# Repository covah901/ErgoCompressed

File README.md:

# ErgoCompressed
Making Ergodone smaller without sacrificing functionality.

based on :ErgoDone

Original work by Dox. K.T.E.C. present.
# Lisence
GPL v3

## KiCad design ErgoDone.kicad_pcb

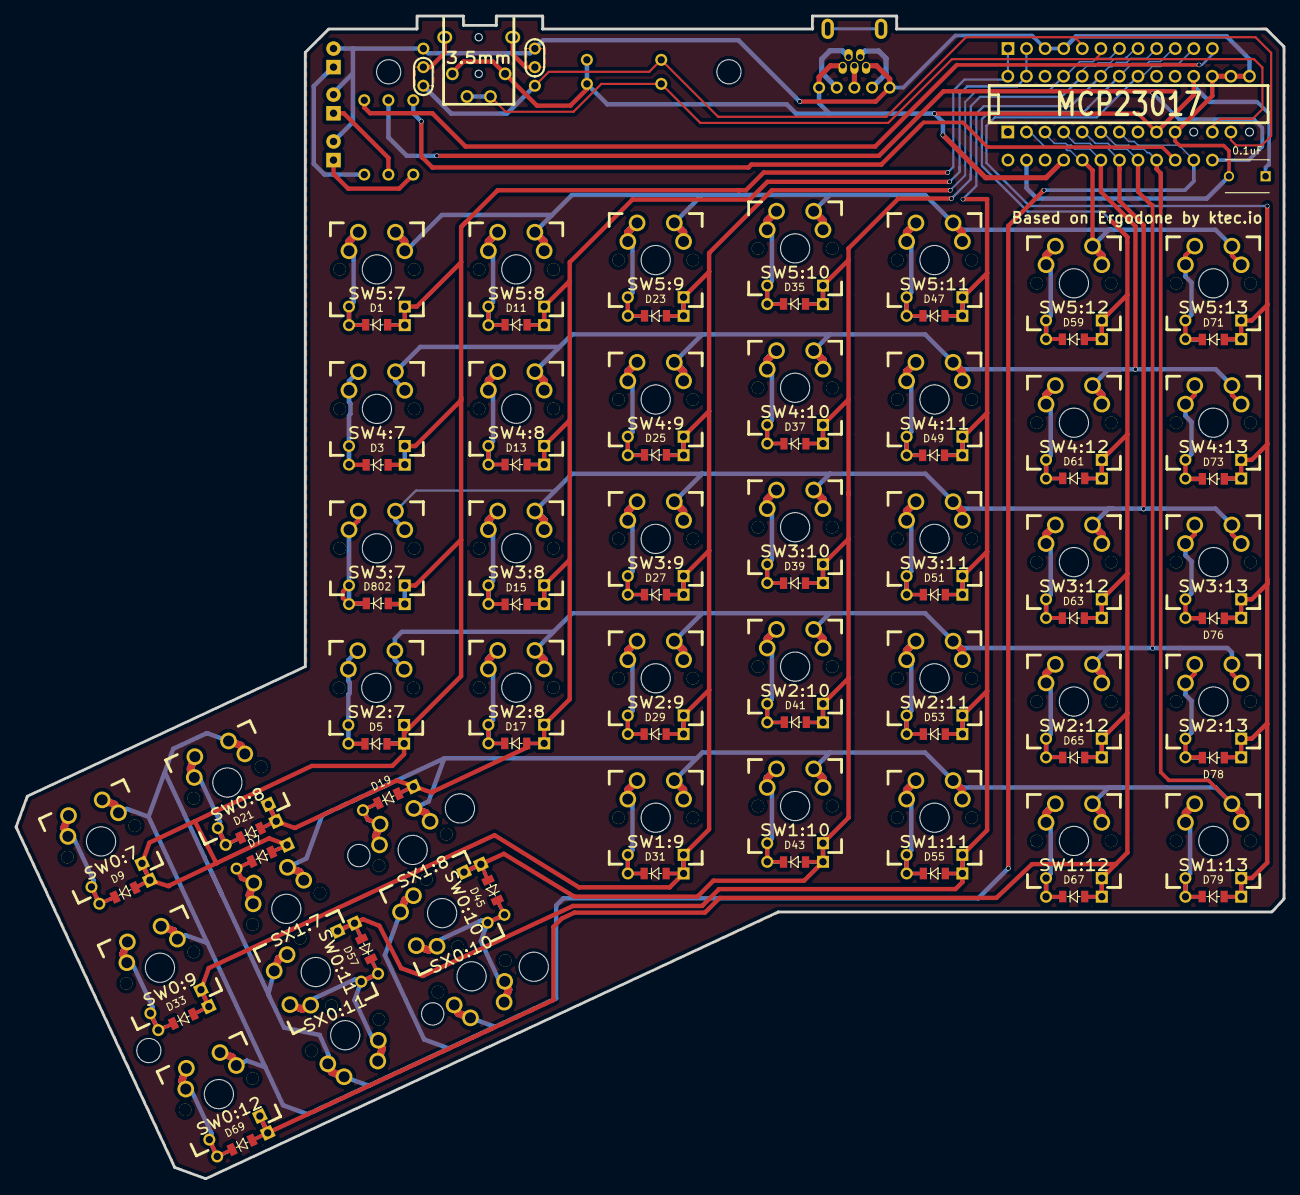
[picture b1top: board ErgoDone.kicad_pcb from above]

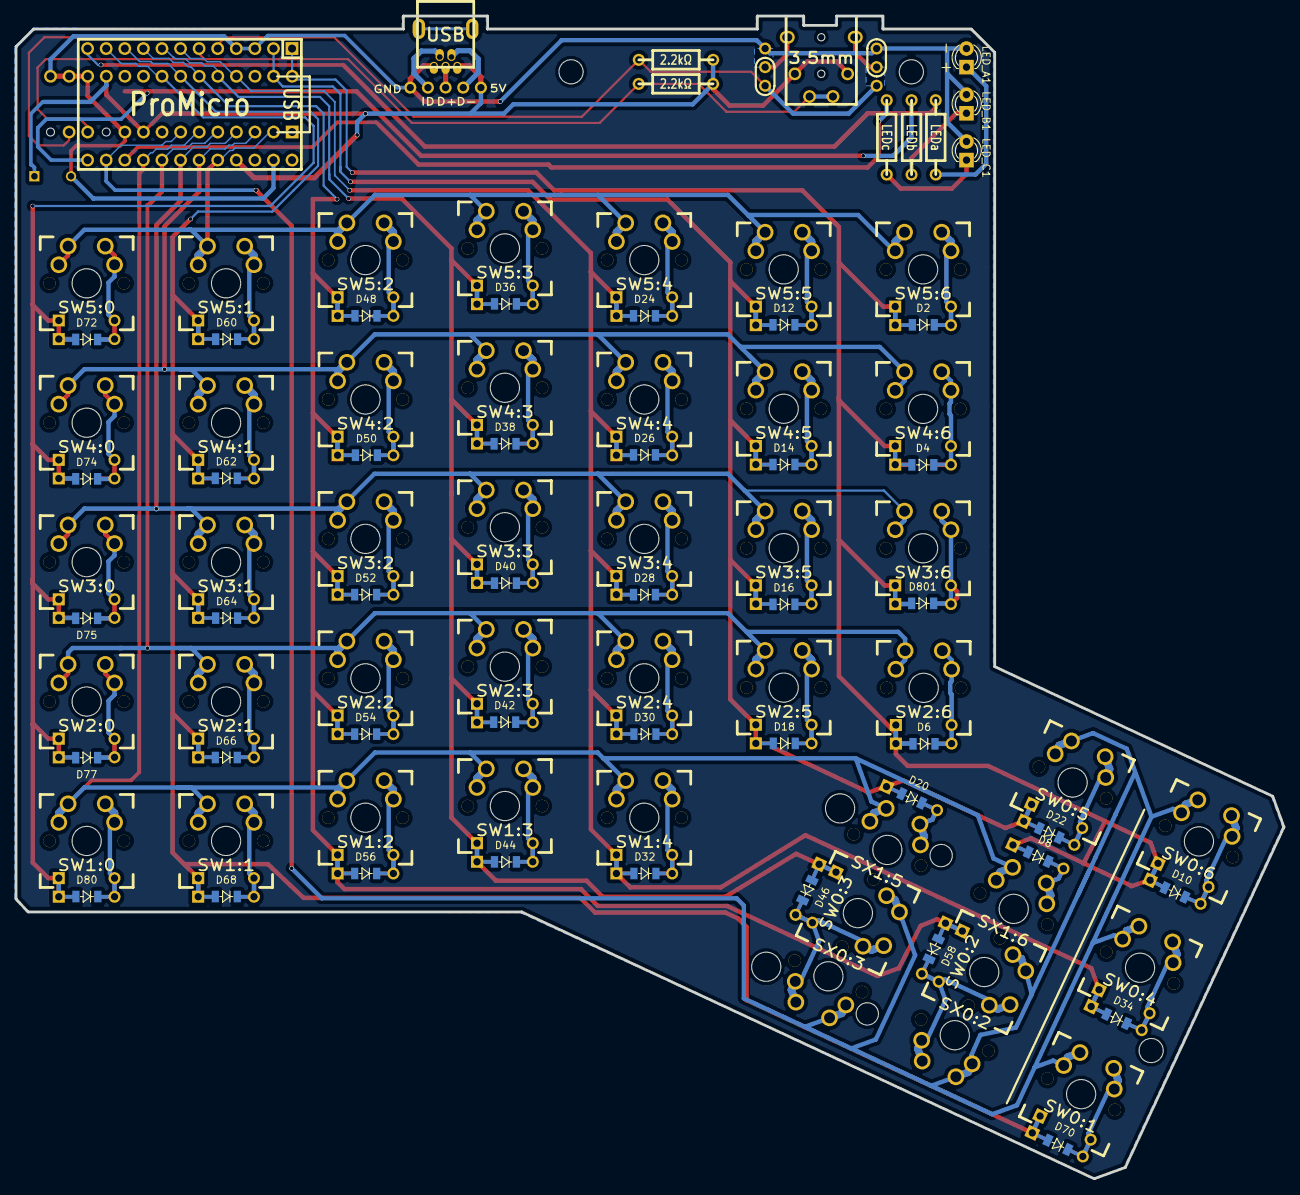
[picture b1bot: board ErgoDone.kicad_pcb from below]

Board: 2 copper layers, 173.3 x 158.9 mm, 143 parts (52 on the bottom side), 66 nets.

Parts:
C1: 0.1uF; C_Disc_D6_P5
D1, D3, D5, D7, D9, D11, D13, D15, D17, D19, D21, D23, D25, D27, D29, D31, D33, D35, D37, D39, D41, D43, D45, D47, D49, D51, D53, D55, D57, D59, D61, D63, D65, D67, D69, D71, D73, D75, D77, D79, D802: DIODE; D_1206_L
D2, D4, D6, D8, D10, D12, D14, D16, D18, D20, D22, D24, D26, D28, D30, D32, D34, D36, D38, D40, D42, D44, D46, D48, D50, D52, D54, D56, D58, D60, D62, D64, D66, D68, D70, D72, D74, D76, D78, D80, D801: DIODE; D_1206_R
D81, D82: DIODE; DIODE_SX
J1: USB; USBMINImod
J2: 3.5mm; 4pin35mmAudio
J3, J4: JMP; 100PITCH1X3
LED_A1: LEDa; ERGO_LED-3MM
LED_B1: LEDb; ERGO_LED-3MM
LED_C1: LEDc; ERGO_LED-3MM
R1, R2: 2.2kΩ; ERGO_RESISTOR
RA1: LEDa; ERGO_RESISTOR
RB1: LEDb; ERGO_RESISTOR
RC1: LEDc; ERGO_RESISTOR
S2: STAB200; STAB_PCB940
SW0:7: SW0:6; MX_FLIP_DIODE_NOSMD
SW0:8: SW0:5; MX_FLIP_DIODE_NOSMD
SW0:9: SW0:4; MX_FLIP_DIODE_NOSMD
SW0:10: SW0:3; MX_FLIP_DIODE_NOSMD
SW0:11: SW0:2; MX_FLIP_DIODE_NOSMD
SW0:12: SW0:1; MX_FLIP_DIODE_NOSMD
SW1:9: SW1:4; MX_FLIP_DIODE_NOSMD
SW1:10: SW1:3; MX_FLIP_DIODE_NOSMD
SW1:11: SW1:2; MX_FLIP_DIODE_NOSMD
SW1:12: SW1:1; MX_FLIP_DIODE_NOSMD
SW1:13: SW1:0; MX_FLIP_DIODE_NOSMD
SW2:7: SW2:6; MX_FLIP_DIODE_NOSMD
SW2:8: SW2:5; MX_FLIP_DIODE_NOSMD
SW2:9: SW2:4; MX_FLIP_DIODE_NOSMD
SW2:10: SW2:3; MX_FLIP_DIODE_NOSMD
SW2:11: SW2:2; MX_FLIP_DIODE_NOSMD
SW2:12: SW2:1; MX_FLIP_DIODE_NOSMD
SW2:13: SW2:0; MX_FLIP_DIODE_NOSMD
SW3:7: SW3:6; MX_FLIP_DIODE_NOSMD
SW3:8: SW3:5; MX_FLIP_DIODE_NOSMD
SW3:9: SW3:4; MX_FLIP_DIODE_NOSMD
SW3:10: SW3:3; MX_FLIP_DIODE_NOSMD
SW3:11: SW3:2; MX_FLIP_DIODE_NOSMD
SW3:12: SW3:1; MX_FLIP_DIODE_NOSMD
SW3:13: SW3:0; MX_FLIP_DIODE_NOSMD
SW4:7: SW4:6; MX_FLIP_DIODE_NOSMD
SW4:8: SW4:5; MX_FLIP_DIODE_NOSMD
SW4:9: SW4:4; MX_FLIP_DIODE_NOSMD
SW4:10: SW4:3; MX_FLIP_DIODE_NOSMD
SW4:11: SW4:2; MX_FLIP_DIODE_NOSMD
SW4:12: SW4:1; MX_FLIP_DIODE_NOSMD
SW4:13: SW4:0; MX_FLIP_DIODE_NOSMD
SW5:7: SW5:6; MX_FLIP_DIODE_NOSMD
SW5:8: SW5:5; MX_FLIP_DIODE_NOSMD
SW5:9: SW5:4; MX_FLIP_DIODE_NOSMD
SW5:10: SW5:3; MX_FLIP_DIODE_NOSMD
SW5:11: SW5:2; MX_FLIP_DIODE_NOSMD
SW5:12: SW5:1; MX_FLIP_DIODE_NOSMD
SW5:13: SW5:0; MX_FLIP_DIODE_NOSMD
SX0:10: SX0:3; MX_FLIP
SX0:11: SX0:2; MX_FLIP
SX1:7: SX1:6; MX_FLIP
SX1:8: SX1:5; MX_FLIP
U1: ProMicro
U2: MCP23017

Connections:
/COL0: D71.2, D72.2, D73.2, D74.2, D75.2, D76.2, D77.2, D78.2, D79.2, D80.2, SW1:13.4, SW2:13.4, SW3:13.4, SW4:13.4, SW5:13.4, U1.11, U2.21
/COL1: D59.2, D60.2, D61.2, D62.2, D63.2, D64.2, D65.2, D66.2, D67.2, D68.2, D69.2, D70.2, SW0:12.4, SW1:12.4, SW2:12.4, SW3:12.4, SW4:12.4, SW5:12.4, U1.10, U2.22
/COL4: D23.2, D24.2, D25.2, D26.2, D27.2, D28.2, D29.2, D30.2, D31.2, D32.2, D33.2, D34.2, SW0:9.4, SW1:9.4, SW2:9.4, SW3:9.4, SW4:9.4, SW5:9.4, U1.7, U2.25
/COL5: D11.2, D12.2, D13.2, D14.2, D15.2, D16.2, D17.2, D18.2, D19.2, D20.2, D21.2, D22.2, D82.2, SW0:8.4, SW2:8.4, SW3:8.4, SW4:8.4, SW5:8.4, U1.2, U2.27
/COL6: D1.2, D2.2, D3.2, D4.2, D5.2, D6.2, D7.2, D8.2, D9.2, D10.2, D81.2, D801.2, D802.2, SW0:7.4, SW2:7.4, SW3:7.4, SW4:7.4, SW5:7.4, U1.1, U2.28
/COL10: D35.2, D36.2, D37.2, D38.2, D39.2, D40.2, D41.2, D42.2, D43.2, D44.2, D45.2, D46.2, SW0:10.4, SW1:10.4, SW2:10.4, SW3:10.4, SW4:10.4, SW5:10.4, U1.8, U2.24
/COL11: D47.2, D48.2, D49.2, D50.2, D51.2, D52.2, D53.2, D54.2, D55.2, D56.2, D57.2, D58.2, SW0:11.4, SW1:11.4, SW2:11.4, SW3:11.4, SW4:11.4, SW5:11.4, U1.9, U2.23
/LED_A: RA1.1, U1.12
/LED_B: RB1.1, U1.18
/LED_C: RC1.1, U1.20
/ROW0: SW0:7.1, SW0:8.1, SW0:9.1, SW0:10.1, SW0:11.1, SW0:12.1, SX0:10.1, SX0:11.1, U1.19, U2.7
/ROW1: SW1:9.1, SW1:10.1, SW1:11.1, SW1:12.1, SW1:13.1, SX1:7.1, SX1:8.1, U1.21, U2.6
/ROW2: SW2:7.1, SW2:8.1, SW2:9.1, SW2:10.1, SW2:11.1, SW2:12.1, SW2:13.1, U1.22, U2.5
/ROW3: SW3:7.1, SW3:8.1, SW3:9.1, SW3:10.1, SW3:11.1, SW3:12.1, SW3:13.1, U1.23, U2.4
/ROW4: SW4:7.1, SW4:8.1, SW4:9.1, SW4:10.1, SW4:11.1, SW4:12.1, SW4:13.1, U1.24, U2.3
/ROW5: SW5:7.1, SW5:8.1, SW5:9.1, SW5:10.1, SW5:11.1, SW5:12.1, SW5:13.1, U1.25, U2.2
/SCLM: J2.3, J2.5, R2.2, U1.6, U2.12
/SDAM: J3.1, J4.1, R1.2, U1.5, U2.13
GND: C1.2, J1.5, J3.3, J4.3, LED_A1.2, LED_B1.2, LED_C1.2, U1.3, U1.4, U1.28, U2.10, U2.15, U2.16, U2.17
unnamed: D1.1, D2.1, SW5:7.2, SW5:7.3
unnamed: D3.1, D4.1, SW4:7.2, SW4:7.3
unnamed: D5.1, D6.1, SW2:7.2, SW2:7.3
unnamed: D7.1, D8.1, D81.1, SX1:7.2
unnamed: D9.1, D10.1, SW0:7.2, SW0:7.3
unnamed: D11.1, D12.1, SW5:8.2, SW5:8.3
unnamed: D13.1, D14.1, SW4:8.2, SW4:8.3
unnamed: D15.1, D16.1, SW3:8.2, SW3:8.3
unnamed: D17.1, D18.1, SW2:8.2, SW2:8.3
unnamed: D19.1, D20.1, D82.1, SX1:8.2
unnamed: D21.1, D22.1, SW0:8.2, SW0:8.3
unnamed: D23.1, D24.1, SW5:9.2, SW5:9.3
unnamed: D25.1, D26.1, SW4:9.2, SW4:9.3
unnamed: D27.1, D28.1, SW3:9.2, SW3:9.3
unnamed: D29.1, D30.1, SW2:9.2, SW2:9.3
unnamed: D31.1, D32.1, SW1:9.2, SW1:9.3
unnamed: D33.1, D34.1, SW0:9.2, SW0:9.3
unnamed: D35.1, D36.1, SW5:10.2, SW5:10.3
unnamed: D37.1, D38.1, SW4:10.2, SW4:10.3
unnamed: D39.1, D40.1, SW3:10.2, SW3:10.3
unnamed: D41.1, D42.1, SW2:10.2, SW2:10.3
unnamed: D43.1, D44.1, SW1:10.2, SW1:10.3
unnamed: D45.1, D46.1, SW0:10.2, SW0:10.3, SX0:10.2
unnamed: D47.1, D48.1, SW5:11.2, SW5:11.3
unnamed: D49.1, D50.1, SW4:11.2, SW4:11.3
unnamed: D51.1, D52.1, SW3:11.2, SW3:11.3
unnamed: D53.1, D54.1, SW2:11.2, SW2:11.3
unnamed: D55.1, D56.1, SW1:11.2, SW1:11.3
unnamed: D57.1, D58.1, SW0:11.2, SW0:11.3, SX0:11.2
unnamed: D59.1, D60.1, SW5:12.2, SW5:12.3
unnamed: D61.1, D62.1, SW4:12.2, SW4:12.3
unnamed: D63.1, D64.1, SW3:12.2, SW3:12.3
unnamed: D65.1, D66.1, SW2:12.2, SW2:12.3
unnamed: D67.1, D68.1, SW1:12.2, SW1:12.3
unnamed: D69.1, D70.1, SW0:12.2, SW0:12.3
unnamed: D71.1, D72.1, SW5:13.2, SW5:13.3
unnamed: D73.1, D74.1, SW4:13.2, SW4:13.3
unnamed: D75.1, D76.1, SW3:13.2, SW3:13.3
unnamed: D77.1, D78.1, SW2:13.2, SW2:13.3
unnamed: D79.1, D80.1, SW1:13.2, SW1:13.3
unnamed: D801.1, D802.1, SW3:7.2, SW3:7.3
unnamed: J2.1, J3.2
unnamed: J2.4, J4.2
unnamed: LED_A1.1, RA1.2
unnamed: LED_B1.1, RB1.2
unnamed: LED_C1.1, RC1.2
VCC: C1.1, J1.1, J2.2, J2.6, R1.1, R2.1, U1.26, U2.9, U2.18

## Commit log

2018-10-17 Changed outer column to 1u and moved capacitor to make more room on the outside edge.
2018-10-17 Added footprint for low profile switch
2018-10-17 update readme file
2018-10-17 Innwards column pads rotate and add one more switch
2018-10-17 Updating net and placing missing diodes.
2018-10-17 Change in PCB size and silkscreen changes.
2018-10-17 Correction on silkscreen and generated up to date gerber files.
2018-10-18 Moving chips and narrowing PCB
2018-10-18 Chamfering corners and generating up-to date gerber files including updated drill maps.
2018-10-21 Update of readme after project name change
2018-10-21 Correcting edge cuts to close the gap in pcb cut.
2018-10-21 Adding 3d render of the work in progress board to illustrate the direction it's being developed in.
2018-10-21 Update to the readme including 3d render of the board
2018-10-21 Routing traces so the inner column of the thumb cluster could be safely removed.
2018-10-24 New cut, adjusting silkscreen, added Przemo-c
2018-10-24 Changed cuts once again, fixed CU fill. Changed names to soldermask not silkscreen.
2018-10-24 Generated up to date gerber files.
2018-10-24 Added mounting plate design
2018-10-24 Updated board 3d render
2018-10-25 Plate corrected for 80/82 layout
2018-11-25 Adding Firmware binary
2018-11-25 Adding QMK source files for ErgoCompressed.
2018-11-25 Update readme.md
    Info about building and flashin firmware added
2018-11-25 Enlarging text on PCB
